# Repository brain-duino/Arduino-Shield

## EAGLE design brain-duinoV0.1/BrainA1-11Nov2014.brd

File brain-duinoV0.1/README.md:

brain-duino V0.1
=======================================

7 Dec 2014

BrainA1-11Nov2014
is brain-duino V0.1 curcuit and PCB

=========================================
“char6BSLED1_analogIN_4chBrain_intwithClock_UNO_Bluetooth_2.ino” is Arduino code for use Arduino AD input. can use for 2 ch mode and 4 ch mode.
512 Hz sampling.
change to 256 Hz sampling need to set Line 209 to comment and use Line 208 : de-comment

============
use brain-duino with Mac IBVA application, can use 512 Hz sampling and 256 Hz sampling.
but use brain-duino with PC BrainBay V1.9.2 application, can use only 256 Hz sampling.
with PC BrainBay V1.7 application can use 512 Hz sampling and 256 Hz sampling.

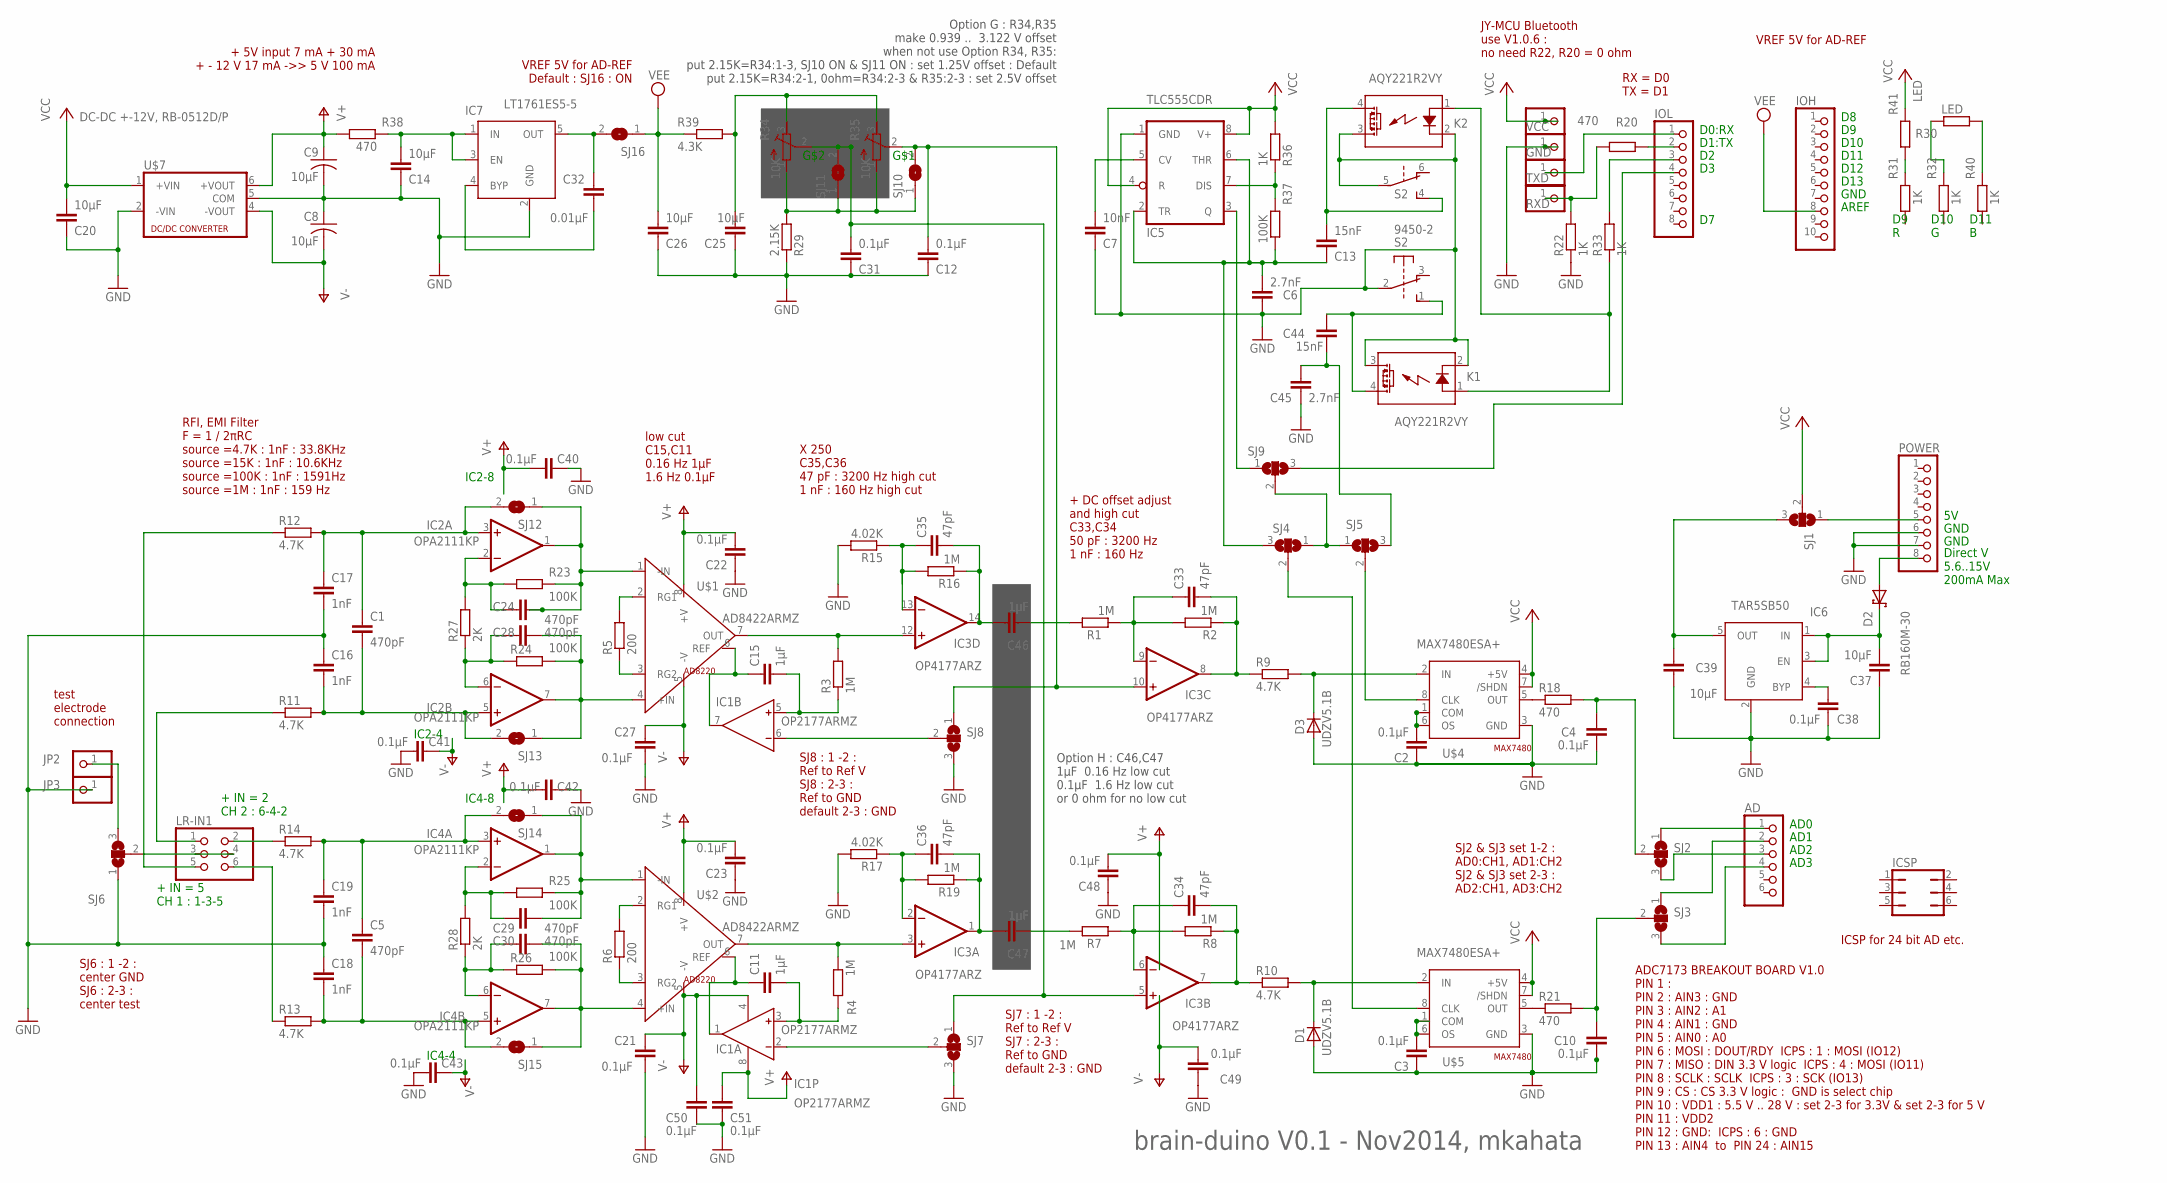
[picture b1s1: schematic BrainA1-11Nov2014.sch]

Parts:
AD: PINHD-1X6; 1X06
C1, C5, C24, C28, C29, C30: 470pF; C0805
C2, C3, C4, C10, C12, C21, C22, C23, C27, C31, C38, C40, C41, C42, C43, C48, C49, C50, C51: 0.1µF; C0805
C6, C45: 2.7nF; C0805
C7: 10nF; C0805
C8, C9, C14, C20, C25, C26, C37, C39: 10µF; C0805
C11, C15, C46, C47: 1µF; C0805
C13, C44: 15nF; C0805
C16, C17, C18, C19: 1nF; C0805
C32: 0.01µF; C0805
C33, C34, C35, C36: 47pF; C0805
D1, D3: UDZV5.1B; SOD110-R
D2: RB160M-30; POWERDI323
GND: PINHD-1X1; 1X01
IC1: OP2177ARMZ; MSOP08
IC2, IC4: OPA2111KP; DIL08
IC3: OP4177ARZ; SO14
IC5: TLC555CDR; SO08
IC6: TAR5SB50; SOT23-5
IC7: LT1761ES5-5; SOT23-5
ICSP: JP3Q
IOH: PINHD-1X10; 1X10
IOL: PINHD-1X8; 1X08
JP2, JP3: PINHD-1X1; 1X01
K1, K2: AQY221R2VY; SSOP4
LR-IN1: PINHD-2X3/90; 2X03/90
POWER: PINHD-1X8; 1X08
R1, R2, R3, R4, R7, R8, R16, R19: 1M; R0805
R5, R6: 200; R0805
R9, R10, R11, R12, R13, R14: 4.7K; R0805
R15, R17: 4.02K; R0805
R18, R20, R21, R38: 470; R0805
R22, R33, R36: 1K; R0805
R23, R24, R25, R26, R37: 100K; R0805
R27, R28: 2K; R0805
R29: 2.15K; R0805
R30, R41: LED; R0402
R31, R32, R40: 1K; R0402
R34, R35: 10K; RTRIM5X
R39: 4.3K; R0805
RXD: PINHD-1X1; 1X01
S2: 9450-2
SJ1, SJ2, SJ3, SJ4, SJ5, SJ6, SJ7, SJ8, SJ9: SJ2W; SJ_2
SJ10, SJ11, SJ12, SJ13, SJ14, SJ15, SJ16: SJ
TXD: PINHD-1X1; 1X01
U$1, U$2: AD8422ARMZ; AD8220
U$4, U$5: MAX7480ESA+; MAX7480
U$7: DC-DC +-12V, RB-0512D/P; RB-0515D
VCC: PINHD-1X1; 1X01

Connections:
GND: C2.1, C3.1, C4.1, C6.1, C7.1, C8.1, C9.2, C10.1, C12.1, C14.1, C16.1, C17.2, C18.1, C19.2, C20.1, C21.2, C22.1, C23.1, C25.1, C26.1, C27.2, C31.1, C37.1, C38.1, C39.1, C40.1, C41.2, C42.2, C43.2, C45.1, C48.1, C49.1, C50.2, C51.2, D1.A, D3.A, GND.1, IC5.1 (GND), IC6.2 (GND), IC7.2 (GND), JP3.1, K1.2 (K), K1.3 (DS2), K2.2 (K), K2.3 (DS2), POWER.6, POWER.7, R15.2, R17.2, R22.1, R29.1, S2.2, S2.5, SJ6.1, SJ7.3, SJ8.3, U$4.3 (GND), U$5.3 (GND), U$7.2 (-VIN), U$7.5 (COM)
LR-IN: LR-IN1.2, R14.1
unnamed: C4.2, R18.2, SJ2.2
unnamed: C34.2, IC3.7 (OUT), R8.1, R10.1
unnamed: C47.2, R7.2
unnamed: C15.2, IC1.5 (IN+), R3.1
unnamed: C24.1, IC2.2 (-IN), R23.1, R27.2
unnamed: C33.1, IC3.9 (-IN), R1.1, R2.2
unnamed: C34.1, IC3.6 (-IN), R7.1, R8.2
unnamed: D3.C, R9.2, U$4.2 (IN)
unnamed: C10.2, R21.2, SJ3.2
unnamed: D1.C, R10.2, U$5.2 (IN)
unnamed: C28.1, IC2.6 (-IN), R24.1, R27.1
unnamed: IC3.12 (+IN), R3.2, U$1.7 (OUT)
unnamed: R20.1, R22.2, RXD.1
unnamed: C24.2, IC2.1 (OUT), R23.2, SJ12.1, U$1.1 (-IN)
unnamed: C15.1, IC1.7 (OUT), U$1.6 (REF)
unnamed: C11.1, IC1.1 (OUT), U$2.6 (REF)
unnamed: C11.2, IC1.3 (IN+), R4.1
unnamed: C35.1, IC3.13 (-IN), R15.1, R16.2
unnamed: R5.1, U$1.3 (RG2)
unnamed: C1.2, C16.2, IC2.5 (+IN), R11.2, SJ13.2
unnamed: C28.2, IC2.7 (OUT), R24.2, SJ13.1, U$1.4 (+IN)
unnamed: C5.1, C19.1, IC4.3 (+IN), R14.2, SJ14.2
unnamed: C13.2, K2.4 (DS1), S2.4 (S)
unnamed: C35.2, C46.1, IC3.14 (OUT), R16.1
unnamed: LR-IN1.6, R13.1
unnamed: C5.2, C18.2, IC4.5 (+IN), R13.2, SJ15.2
unnamed: C36.1, IC3.2 (-IN), R17.1, R19.2
unnamed: C36.2, C47.1, IC3.1 (OUT), R19.1
unnamed: IOL.2, R20.2
unnamed: R5.2, U$1.2 (RG1)
unnamed: IOL.1, TXD.1
unnamed: C33.2, IC3.8 (OUT), R2.1, R9.1
unnamed: LR-IN1.5, R12.1
unnamed: AD.1, SJ2.1
unnamed: C2.2, U$4.1 (COM), U$4.6 (OS)
unnamed: C29.1, IC4.2 (-IN), R25.1, R28.2
unnamed: C3.2, U$5.1 (COM), U$5.6 (OS)
unnamed: C30.1, IC4.6 (-IN), R26.1, R28.1
unnamed: C29.2, IC4.1 (OUT), R25.2, SJ14.1, U$2.1 (-IN)
unnamed: R6.2, U$2.2 (RG1)
unnamed: C30.2, IC4.7 (OUT), R26.2, SJ15.1, U$2.4 (+IN)
unnamed: R18.1, U$4.5 (OUT)
unnamed: AD.2, SJ3.1
unnamed: AD.3, SJ2.3
unnamed: AD.4, SJ3.3
unnamed: IC3.3 (+IN), R4.2, U$2.7 (OUT)
unnamed: C38.2, IC6.4 (BYP)
unnamed: LR-IN1.1, R11.1
unnamed: IOL.3, R33.2
unnamed: R6.1, U$2.3 (RG2)
unnamed: C1.1, C17.1, IC2.3 (+IN), R12.2, SJ12.2
unnamed: C14.2, IC7.1 (IN), IC7.3 (EN), R38.2
unnamed: R21.1, U$5.5 (OUT)
unnamed: C37.2, D2.C, IC6.1 (IN), IC6.3 (EN)
unnamed: C31.2, IC3.5 (+IN), R34.2 (S), SJ7.1, SJ11.2
unnamed: K1.1 (A), K2.1 (A), R33.1
unnamed: C25.2, R34.3 (A), R35.3 (A), R39.2
unnamed: JP2.1, SJ6.3
unnamed: IC5.7 (DIS), R36.1, R37.2
unnamed: C6.2, C13.1, IC5.2 (TR), IC5.6 (THR), R37.1, SJ4.3
unnamed: LR-IN1.3, LR-IN1.4, SJ6.2
unnamed: C32.1, IC7.4 (BYP)
unnamed: C7.2, IC5.5 (CV)
unnamed: C39.2, IC6.5 (OUT), SJ1.3
unnamed: POWER.5, SJ1.1
unnamed: R29.2, R34.1 (E), R35.1 (E), SJ10.1, SJ11.1
unnamed: SJ5.2, U$4.8 (CLK)
unnamed: SJ4.2, U$5.8 (CLK)
unnamed: IC5.3 (Q), SJ9.1
unnamed: C44.1, C45.2, SJ5.3
unnamed: C44.2, K1.4 (DS1), S2.1 (S)
unnamed: R31.2, R41.1
unnamed: R30.2, R32.2
unnamed: R30.1, R40.2
unnamed: C46.2, R1.2
unnamed: D2.A, POWER.8
unnamed: IC1.2 (IN-), SJ7.2
unnamed: C12.2, IC3.10 (+IN), R35.2 (S), SJ8.1, SJ10.2
unnamed: IC1.6 (IN-), SJ8.2
unnamed: SJ4.1, SJ5.1, SJ9.2
unnamed: IOL.4, SJ9.3
unnamed: C32.2, IC7.5 (OUT), SJ16.2
V+: C9.1, C22.2, C23.2, C40.2, C42.1, C48.2, C51.1, IC1.8 (V+), IC2.8 (V+), IC3.4 (V+), IC4.8 (V+), R38.1, U$1.8 (+V), U$2.8 (+V), U$7.6 (+VOUT)
V-: C8.2, C21.1, C27.1, C41.1, C43.1, C49.2, C50.1, IC1.4 (V-), IC2.4 (V-), IC3.11 (V-), IC4.4 (V-), U$1.5 (-V), U$2.5 (-V), U$7.4 (-VOUT)
VCC: C20.2, IC5.4 (R), IC5.8 (V+), R36.2, R41.2, SJ1.2, U$4.4 (+5V), U$4.7 (/SHDN), U$5.4 (+5V), U$5.7 (/SHDN), U$7.1 (+VIN), VCC.1
VEE: C26.2, IOH.8, R39.1, SJ16.1

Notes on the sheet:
JY-MCU Bluetooth use V1.0.6 : no need R22, R20 = 0 ohm
X 250 C35,C36 47 pF : 3200 Hz high cut 1 nF : 160 Hz high cut
+ DC offset adjust and high cut C33,C34 50 pF : 3200 Hz 1 nF : 160 Hz
RFI, EMI Filter F = 1 / 2πRC source =4.7K : 1nF : 33.8KHz source =15K : 1nF : 10.6KHz source =100K : 1nF : 1591Hz source =1M : 1nF : 159 Hz
low cut C15,C11 0.16 Hz 1µF 1.6 Hz 0.1µF
+ IN = 5 CH 1 : 1-3-5
+ IN = 2 CH 2 : 6-4-2
+ 5V input 7 mA + 30 mA + - 12 V 17 mA ->> 5 V 100 mA
RX = D0 TX = D1
SJ2 & SJ3 set 1-2 : AD0:CH1, AD1:CH2 SJ2 & SJ3 set 2-3 : AD2:CH1, AD3:CH2
Option G : R34,R35 make 0.939 .. 3.122 V offset when not use Option R34, R35: put 2.15K=R34:1-3, SJ10 ON & SJ11 ON : set 1.25V offset : Default put 2.15K=R34:2-1, 0ohm=R34:2-3 & R35:2-3 : set 2.5V offset
G$1
G$2
VREF 5V for AD-REF Default : SJ16 : ON
VREF 5V for AD-REF
D0:RX
D1:TX
D13
D12
AREF
GND
AD0
AD1
AD2
AD3
Direct V 5.6..15V 200mA Max
D10
D11
D9 R
D10 G
D11 B
Option H : C46,C47 1µF 0.16 Hz low cut 0.1µF 1.6 Hz low cut or 0 ohm for no low cut
SJ6 : 1 -2 : center GND SJ6 : 2-3 : center test
SJ7 : 1 -2 : Ref to Ref V SJ7 : 2-3 : Ref to GND default 2-3 : GND
test electrode connection
SJ8 : 1 -2 : Ref to Ref V SJ8 : 2-3 : Ref to GND default 2-3 : GND
ICSP for 24 bit AD etc.
ADC7173 BREAKOUT BOARD V1.0 PIN 1 : PIN 2 : AIN3 : GND PIN 3 : AIN2 : A1 PIN 4 : AIN1 : GND PIN 5 : AIN0 : A0 PIN 6 : MOSI : DOUT/RDY ICPS : 1 : MOSI (IO12) PIN 7 : MISO : DIN 3.3 V logic ICPS : 4 : MOSI (IO11) PIN 8 : SCLK : SCLK ICPS : 3 : SCK (IO13) PIN 9 : CS : CS 3.3 V logic : GND is select ch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
IC2-8
IC2-4

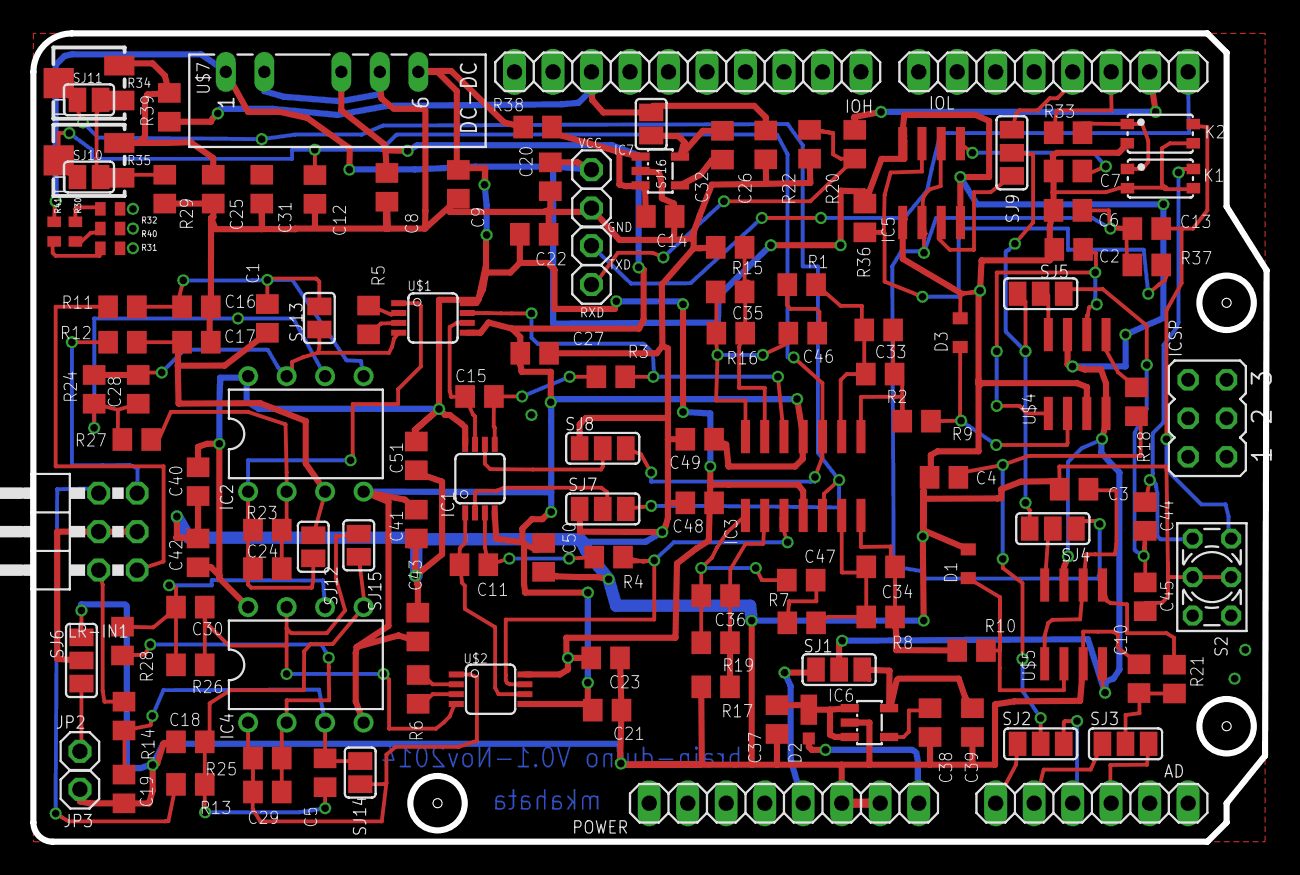
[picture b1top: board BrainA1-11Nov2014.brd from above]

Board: 2 copper layers, 81.4 x 53.3 mm, 138 parts (0 on the bottom side), 88 nets.

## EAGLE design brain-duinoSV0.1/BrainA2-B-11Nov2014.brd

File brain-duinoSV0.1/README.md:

brain-duino S V0.1
=======================================

1 March 2015

BrainA2-A-11Nov2014
BrainA2-B-11Nov2014
is brain-duino S V0.1 curcuit and PCB

=========================================
“char6BSLED1_analogIN_4chBrain_intwithClock_UNO_Bluetooth_2.ino” is Arduino code for use Arduino AD input. can use for 2 ch mode and 4 ch mode.
512 Hz sampling.
change to 256 Hz sampling need to set Line 209 to comment and use Line 208 : de-comment

============
use brain-duino with Mac IBVA application, can use 512 Hz sampling and 256 Hz sampling.
but use brain-duino with PC BrainBay V1.9.2 application, can use only 256 Hz sampling.
with PC BrainBay V1.7 application can use 512 Hz sampling and 256 Hz sampling.

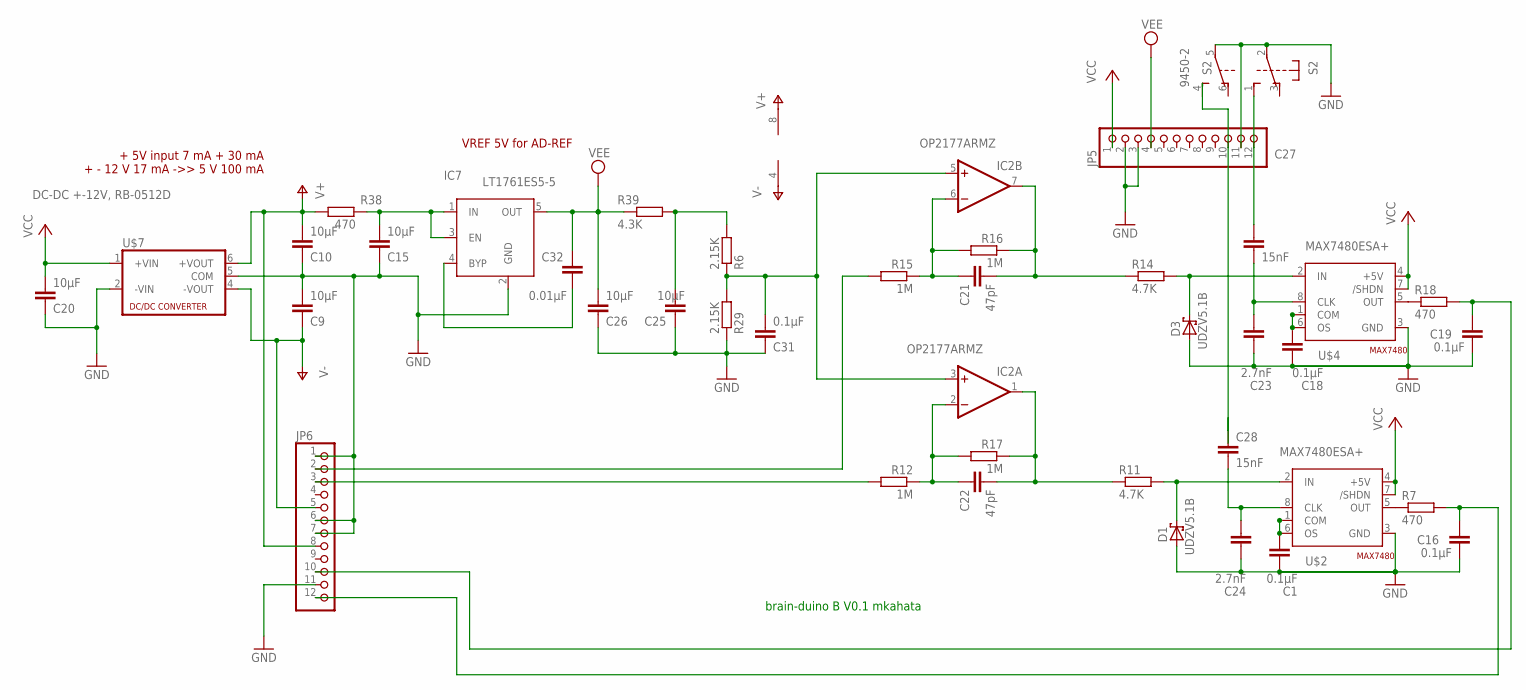
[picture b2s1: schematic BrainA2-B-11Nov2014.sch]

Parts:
C1, C16, C18, C19, C31: 0.1µF; C0603
C9, C10, C15, C20, C25, C26: 10µF; C0603
C21, C22: 47pF; C0603
C23, C24: 2.7nF; C0603
C27, C28: 15nF; C0603
C32: 0.01µF; C0603
D1, D3: UDZV5.1B; SOD323_ST
IC2: OP2177ARMZ; MSOP08
IC7: LT1761ES5-5; SOT23-5
JP5, JP6: PINHD-1X12; 1X12
R6, R29: 2.15K; R0603
R7, R18, R38: 470; R0603
R11, R14: 4.7K; R0603
R12, R15, R16, R17: 1M; R0603
R39: 4.3K; R0603
S2: 9450-2
U$2, U$4: MAX7480ESA+; MAX7480
U$7: DC-DC +-12V, RB-0512D; RB-0515D

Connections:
GND: C1.1, C9.2, C10.1, C15.1, C16.1, C18.1, C19.1, C20.1, C23.1, C24.1, C25.1, C26.1, C31.1, D1.A, D3.A, IC7.2 (GND), JP5.2, JP5.3, JP5.11, JP6.1, JP6.6, JP6.7, JP6.11, R29.1, S2.2, S2.5, U$2.3 (GND), U$4.3 (GND), U$7.2 (-VIN), U$7.5 (COM)
unnamed: C16.2, JP6.12, R7.2
unnamed: C1.2, U$2.1 (COM), U$2.6 (OS)
unnamed: C19.2, JP6.10, R18.2
unnamed: D3.C, R14.2, U$4.2 (IN)
unnamed: R7.1, U$2.5 (OUT)
unnamed: D1.C, R11.2, U$2.2 (IN)
unnamed: C24.2, C28.2, U$2.8 (CLK)
unnamed: C22.1, IC2.2 (-IN), R12.1, R17.2
unnamed: JP6.2, R15.2
unnamed: JP6.3, R12.2
unnamed: C22.2, IC2.1 (OUT), R11.1, R17.1
unnamed: C21.1, IC2.6 (-IN), R15.1, R16.2
unnamed: C21.2, IC2.7 (OUT), R14.1, R16.1
unnamed: C27.1, JP5.12, S2.1 (S)
unnamed: C28.1, JP5.10, S2.4 (S)
unnamed: C18.2, U$4.1 (COM), U$4.6 (OS)
unnamed: R18.1, U$4.5 (OUT)
unnamed: C15.2, IC7.1 (IN), IC7.3 (EN), R38.2
unnamed: C25.2, R6.2, R39.2
unnamed: C32.1, IC7.4 (BYP)
unnamed: C31.2, IC2.3 (+IN), IC2.5 (+IN), R6.1, R29.2
unnamed: C23.2, C27.2, U$4.8 (CLK)
V+: C10.2, IC2.8 (V+), JP6.8, R38.1, U$7.6 (+VOUT)
V-: C9.1, IC2.4 (V-), JP6.5, U$7.4 (-VOUT)
VCC: C20.2, JP5.1, U$2.4 (+5V), U$2.7 (/SHDN), U$4.4 (+5V), U$4.7 (/SHDN), U$7.1 (+VIN)
VEE: C26.2, C32.2, IC7.5 (OUT), JP5.4, R39.1

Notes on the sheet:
+ 5V input 7 mA + 30 mA + - 12 V 17 mA ->> 5 V 100 mA
VREF 5V for AD-REF
brain-duino B V0.1 mkahata

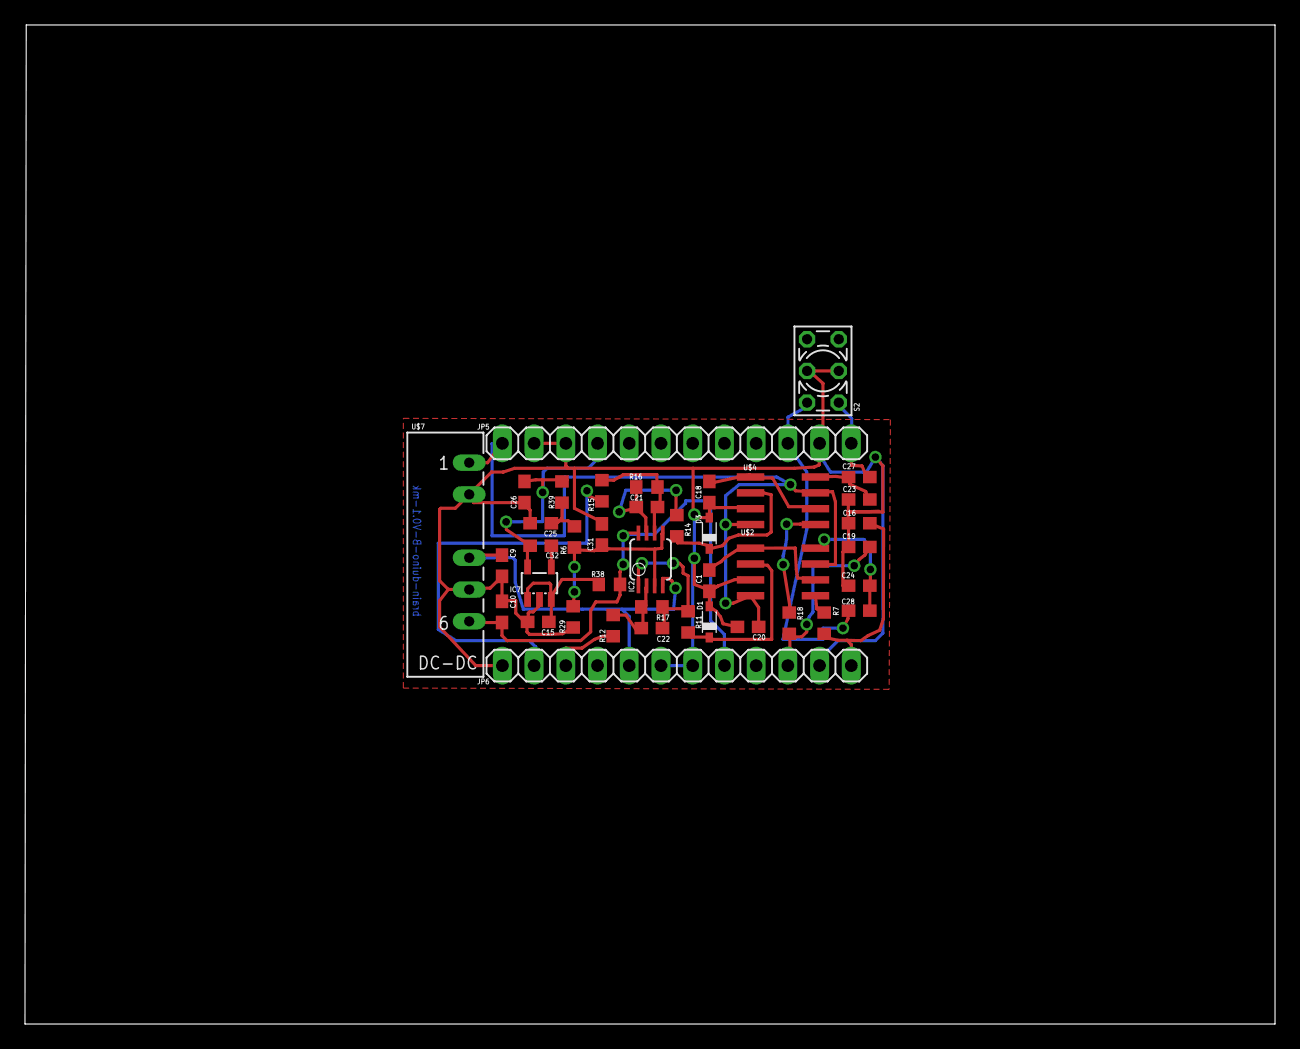
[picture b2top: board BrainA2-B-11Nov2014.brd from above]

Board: 2 copper layers, 100.1 x 80.0 mm, 40 parts (0 on the bottom side), 27 nets.

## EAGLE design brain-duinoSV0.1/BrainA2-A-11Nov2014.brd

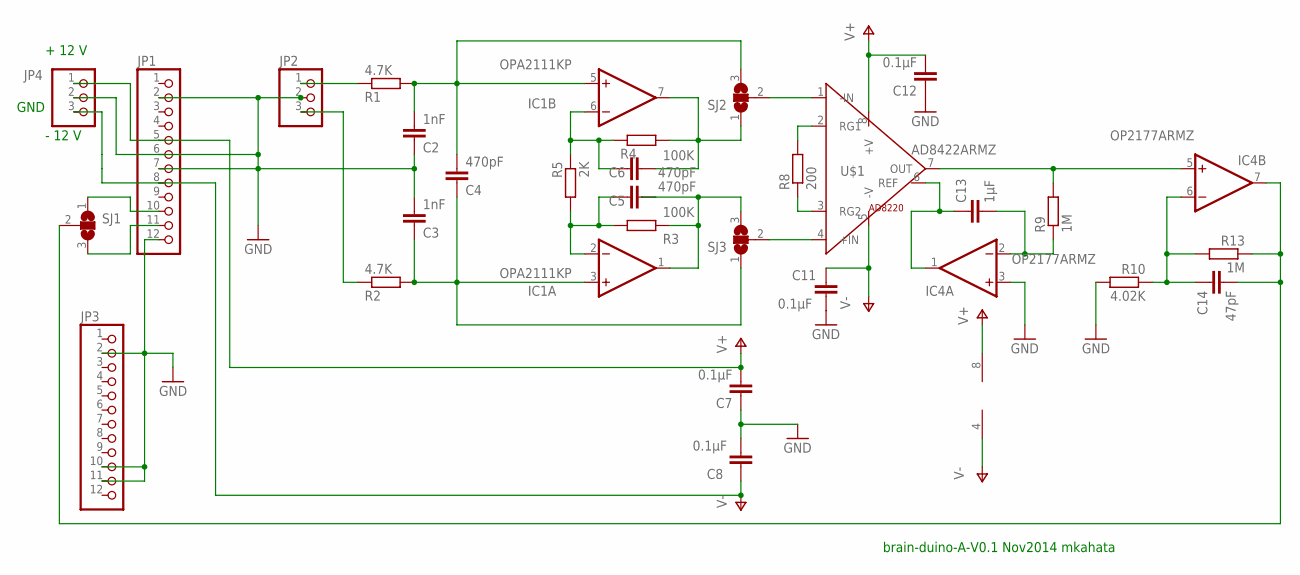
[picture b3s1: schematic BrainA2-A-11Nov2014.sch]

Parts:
C2, C3: 1nF; C0603
C4, C5, C6: 470pF; C0603
C7, C8, C11, C12: 0.1µF; C0603
C13: 1µF; C0603
C14: 47pF; C0603
IC1: OPA2111KP; DIL08
IC4: OP2177ARMZ; MSOP08
JP1, JP3: PINHD-1X12; 1X12
JP2, JP4: PINHD-1X3; 1X03
R1, R2: 4.7K; R0603
R3, R4: 100K; R0603
R5: 2K; R0603
R8: 200; R0603
R9, R13: 1M; R0603
R10: 4.02K; R0603
SJ1, SJ2, SJ3: SJ2W; SJ_2
U$1: AD8422ARMZ; AD8220

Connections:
GND: C2.1, C3.2, C7.1, C8.2, C11.2, C12.1, IC4.3 (+IN), JP1.2, JP1.6, JP1.7, JP1.12, JP2.2, JP3.2, JP3.10, JP3.11, JP4.2, R10.2
unnamed: JP2.1, R1.1
unnamed: JP1.11, SJ1.3
unnamed: JP2.3, R2.1
unnamed: C3.1, C4.1, IC1.3 (+IN), R2.2, SJ3.1
unnamed: C2.2, C4.2, IC1.5 (+IN), R1.2, SJ2.3
unnamed: JP1.10, SJ1.1
unnamed: C5.1, IC1.2 (-IN), R3.1, R5.2
unnamed: C6.1, IC1.6 (-IN), R4.1, R5.1
unnamed: SJ2.2, U$1.1 (-IN)
unnamed: SJ3.2, U$1.4 (+IN)
unnamed: C5.2, IC1.1 (OUT), R3.2, SJ3.3
unnamed: C6.2, IC1.7 (OUT), R4.2, SJ2.1
unnamed: R8.1, U$1.3 (RG2)
unnamed: R8.2, U$1.2 (RG1)
unnamed: IC4.5 (+IN), R9.2, U$1.7 (OUT)
unnamed: C13.2, IC4.2 (-IN), R9.1
unnamed: C14.1, IC4.6 (-IN), R10.1, R13.2
unnamed: C14.2, IC4.7 (OUT), R13.1, SJ1.2
unnamed: C13.1, IC4.1 (OUT), U$1.6 (REF)
V+: C7.2, C12.2, IC1.8 (V+), IC4.8 (V+), JP1.5, JP4.1, U$1.8 (+V)
V-: C8.1, C11.1, IC1.4 (V-), IC4.4 (V-), JP1.8, JP4.3, U$1.5 (-V)

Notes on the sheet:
+ 12 V
- 12 V
GND
brain-duino-A-V0.1 Nov2014 mkahata

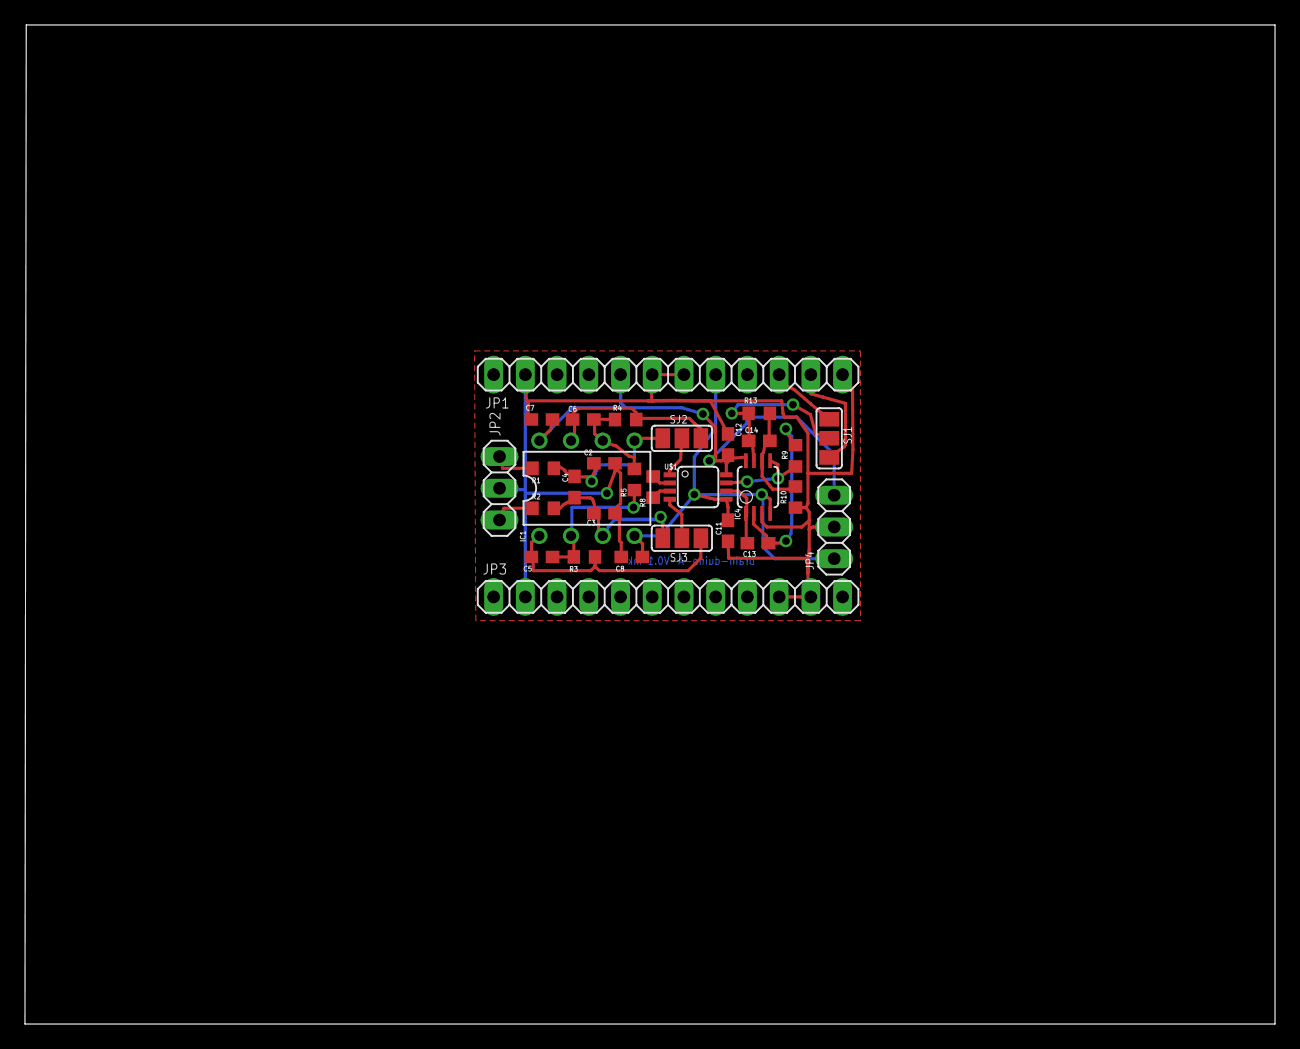
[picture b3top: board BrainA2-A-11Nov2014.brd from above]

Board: 2 copper layers, 100.1 x 80.0 mm, 30 parts (0 on the bottom side), 22 nets.

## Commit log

2015-08-14 initial
2015-08-14 test1
2015-08-14 test2
2015-08-14 test3
